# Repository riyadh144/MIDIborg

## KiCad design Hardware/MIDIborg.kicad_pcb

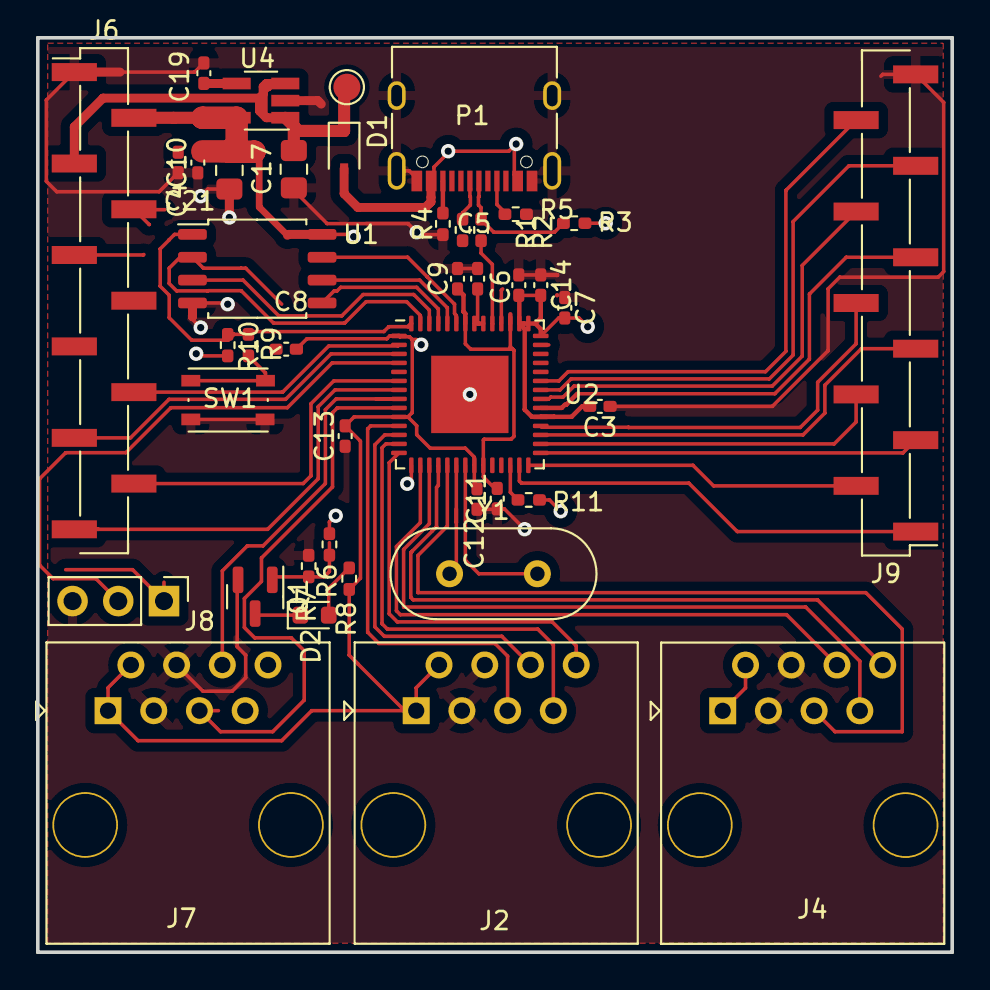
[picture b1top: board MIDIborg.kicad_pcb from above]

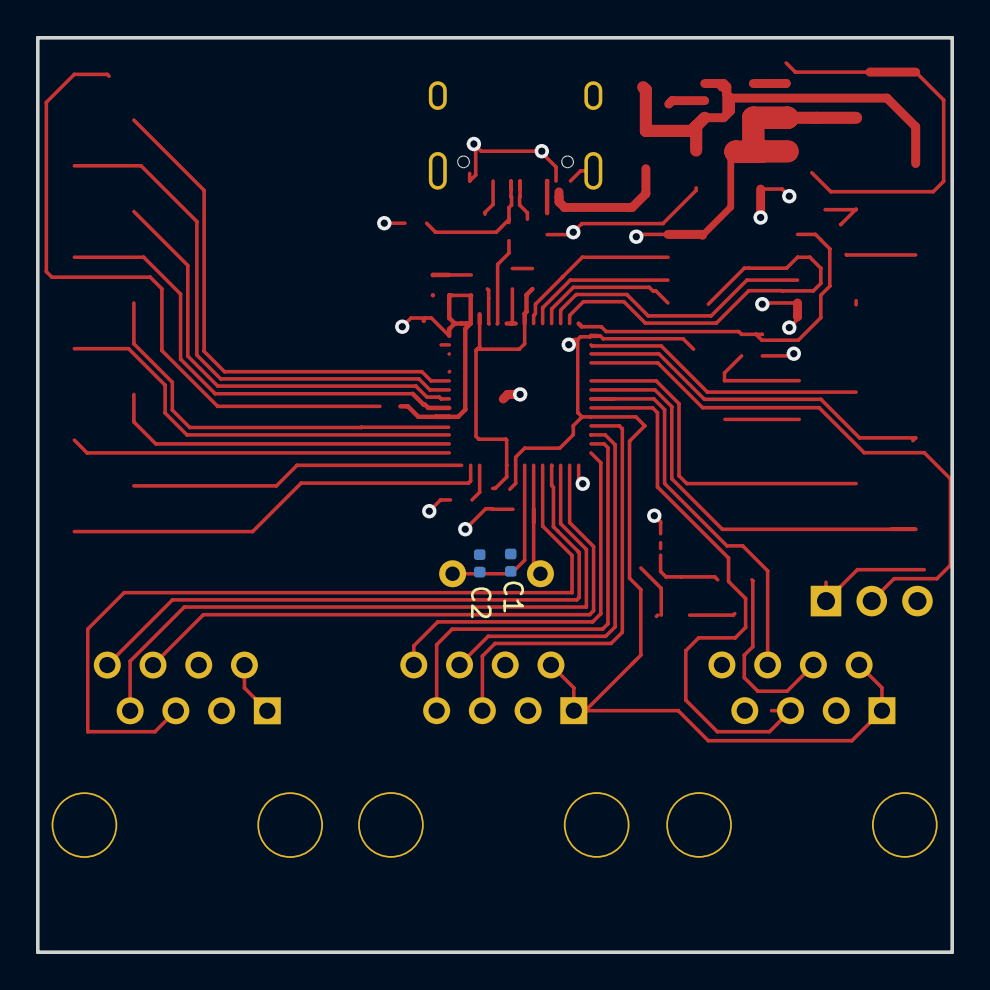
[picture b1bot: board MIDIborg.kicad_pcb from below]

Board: 4 copper layers, 50.8 x 50.8 mm, 44 parts (2 on the bottom side), 52 nets.

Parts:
C1, C2: 18pF; L_0402_1005Metric
C3, C4, C5, C6, C7, C8, C9, C10, C11, C12, C13, C14: .1uF; C_0402_1005Metric_Pad0.74x0.62mm_HandSolder
C17, C21: 1uF; C_0805_2012Metric_Pad1.18x1.45mm_HandSolder
C19: 10nF; C_0402_1005Metric_Pad0.74x0.62mm_HandSolder
D1: 1N5817; D_SOD-323
D2: Red LED; LED_0603_1608Metric
J2, J4, J7: 8P8C; RJ45_OST_PJ012-8P8CX_Vertical
J6, J9: Conn_01x11; PinHeader_1x11_P2.54mm_Vertical_SMD_Pin1Left
J8: Conn_01x03; PinHeader_1x03_P2.54mm_Vertical
P1: USB_C_Plug_USB2.0; USB_C_Receptacle_XKB_U262-16XN-4BVC11
Q1: 2N7002; SOT-23
R1, R2: 27; R_0402_1005Metric_Pad0.72x0.64mm_HandSolder
R3: 1K5; R_0402_1005Metric_Pad0.72x0.64mm_HandSolder
R4, R5: 5k1; R_0402_1005Metric_Pad0.72x0.64mm_HandSolder
R6, R8, R9: 1K; R_0402_1005Metric_Pad0.72x0.64mm_HandSolder
R7: DNP; R_0402_1005Metric_Pad0.72x0.64mm_HandSolder
R10, R11: 10K; R_0402_1005Metric_Pad0.72x0.64mm_HandSolder
SW1: SW_Push; SW_Push_1P1T_NO_Vertical_Wuerth_434133025816
TP2: TestPoint; TestPoint_Pad_D1.5mm
U1: W25Q16JVSSIQ; SOIC-8_5.23x5.23mm_P1.27mm
U2: RP2040; QFN-56-1EP_8x8mm_P0.5mm_EP4.3x4.3mm
U4: BCT2028EUK33; SOT-23-5_HandSoldering
Y1: Crystal; Crystal_HC49-4H_Vertical

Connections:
+3V3: C3.2, C4.2, C5.2, C6.2, C7.2, C8.2, C10.2, C12.2, C13.2, C14.2, C21.2, J2.1, J2.2, J4.1, J4.2, J6.2, J7.1, J7.2, R3.1, R8.1, R10.1, R11.1, U1.8 (VCC), U2.1 (IOVDD), U2.10 (IOVDD), U2.22 (IOVDD), U2.33 (IOVDD), U2.42 (IOVDD), U2.43 (ADC_AVDD), U2.44 (VREG_VIN), U2.48 (USB_VDD), U2.49 (IOVDD), U4.5 (OUT)
+5V: C17.2, D1.1 (K), J6.3, TP2.1, U4.1 (IN), U4.3 (EN)
/1.1V: C9.2, C11.2, U2.23 (DVDD), U2.45 (VREG_VOUT), U2.50 (DVDD)
/GPIO0: J6.8, U2.2 (GPIO0)
/GPIO1: J6.9, U2.3 (GPIO1)
/GPIO4: J6.10, U2.6 (GPIO4)
/GPIO5: J6.11, U2.7 (GPIO5)
/GPIO16: J9.1, U2.27 (GPIO16)
/GPIO17: J9.2, U2.28 (GPIO17)
/GPIO18: J9.3, U2.29 (GPIO18)
/GPIO19: J9.4, U2.30 (GPIO19)
/GPIO20: J9.5, U2.31 (GPIO20)
/GPIO21: J9.6, U2.32 (GPIO21)
/GPIO22: J9.7, U2.34 (GPIO22)
/GPIO23: J9.8, U2.35 (GPIO23)
/GPIO24: J9.9, U2.36 (GPIO24)
/GPIO25: J9.10, U2.37 (GPIO25)
/LED1: R6.2, U2.15 (GPIO12)
/QSPI-CLK: U1.6 (CLK), U2.52 (QSPI_SCLK)
/QSPI-CS: R9.2, R10.2, U1.1 (~CS), U2.56 (QSPI_SS_N)
/QSPI-SD0: U1.5 (DI(IO0)), U2.53 (QSPI_SD0)
/QSPI-SD1: U1.2 (DO(IO1)), U2.55 (QSPI_SD1)
/QSPI-SD2: U1.3 (IO2), U2.54 (QSPI_SD2)
/QSPI-SD3: U1.7 (IO3), U2.51 (QSPI_SD3)
/SCL0: J7.5, U2.9 (GPIO7)
/SDA0: J7.6, U2.8 (GPIO6)
/SPI0_MISO: J4.6, U2.16 (GPIO13)
/SPI0_MOSI: J4.5, U2.19 (TESTEN)
/SPI0_NSS: J4.7, U2.17 (GPIO14)
/SPI0_SCK: J4.8, U2.18 (GPIO15)
/SPI1_MISO: J2.6, U2.12 (GPIO9)
/SPI1_MOSI: J2.5, U2.11 (GPIO8)
/SPI1_NSS: J2.7, U2.13 (GPIO10)
/SPI1_SCK: J2.8, U2.14 (GPIO11)
/UART1_RX: J8.1, U2.5 (GPIO3)
/UART1_TX: J8.2, U2.4 (GPIO2)
/USB_BOOT: R9.1, SW1.1
/d+: R2.1, U2.47 (USB_DP)
/d-: R1.2, U2.46 (USB_DM)
/dd+: P1.A6 (D+), R2.2, R3.2
/dd-: P1.A7 (D-), R1.1
GND: C1.2, C2.2, C3.1, C4.1, C5.1, C6.1, C7.1, C8.1, C9.1, C10.1, C11.1, C12.1, C13.1, C14.1, C17.1, C19.1, C21.1, J2.3, J2.4, J4.3, J4.4, J6.1, J7.3, J7.4, J8.3, J9.11, P1.A1 (GND), P1.A12 (GND), P1.B1 (GND), P1.B12 (GND), P1.S1 (SHIELD), Q1.2 (S), R4.2, R5.2, R7.2, SW1.2, U1.4 (GND), U2.57 (GND), U4.2 (GND)
unnamed: C1.1, U2.20 (XIN), Y1.1
unnamed: C2.1, U2.21 (XOUT), Y1.2
unnamed: C19.2, U4.4 (BP)
unnamed: D1.2 (A), P1.A4 (VBUS), P1.A9 (VBUS), P1.B4 (VBUS), P1.B9 (VBUS)
unnamed: D2.1 (K), Q1.3 (D)
unnamed: D2.2 (A), R8.2
unnamed: P1.A5 (CC), R5.1
unnamed: P1.B5 (VCONN), R4.1
unnamed: Q1.1 (G), R6.1, R7.1
unnamed: R11.2, U2.26 (RUN)

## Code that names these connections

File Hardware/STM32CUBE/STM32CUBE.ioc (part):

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Mcu.Name=STM32F411V(C-E)Tx
Mcu.Package=LQFP100
Mcu.UserName=STM32F411VETx
PA0-WKUP.Signal=ADCx_IN0
PA1.Signal=ADCx_IN1
PA10.Mode=Asynchronous
PA10.Signal=USART1_RX
PA11.Mode=Device_Only
PA11.Signal=USB_OTG_FS_DM
PA12.Mode=Device_Only
PA12.Signal=USB_OTG_FS_DP
PA15.Mode=NSS_Signal_Hard_Output
PA15.Signal=SPI1_NSS
PA2.Signal=ADCx_IN2
PA3.Signal=ADCx_IN3
PA4.Signal=ADCx_IN4
PA5.Signal=ADCx_IN5
PA6.Signal=ADCx_IN6
PA7.Signal=ADCx_IN7
PA9.Mode=Asynchronous
PA9.Signal=USART1_TX
PB0.Signal=ADCx_IN8
PB1.Signal=ADCx_IN9
PB3.Mode=Full_Duplex_Master
PB3.Signal=SPI1_SCK
PB4.Mode=Full_Duplex_Master
PB4.Signal=SPI1_MISO
PB5.Mode=Full_Duplex_Master
PB5.Signal=SPI1_MOSI
PC0.Signal=ADCx_IN10
PC1.Signal=ADCx_IN11
PC10.Mode=SD_4_bits_Wide_bus
PC10.Signal=SDIO_D2
PC11.Mode=SD_4_bits_Wide_bus
PC11.Signal=SDIO_D3
PC12.Mode=SD_4_bits_Wide_bus
PC12.Signal=SDIO_CK
PC2.Signal=ADCx_IN12
PC3.Signal=ADCx_IN13
PC4.Signal=ADCx_IN14
PC5.Signal=ADCx_IN15
PC8.Mode=SD_4_bits_Wide_bus
PC8.Signal=SDIO_D0
PC9.Mode=SD_4_bits_Wide_bus
PC9.Signal=SDIO_D1
PD2.Mode=SD_4_bits_Wide_bus
PD2.Signal=SDIO_CMD
PH0\ -\ OSC_IN.Mode=HSE-External-Oscillator
PH0\ -\ OSC_IN.Signal=RCC_OSC_IN
PH1\ -\ OSC_OUT.Mode=HSE-External-Oscillator
PH1\ -\ OSC_OUT.Signal=RCC_OSC_OUT
RCC.HSE_VALUE=8000000
RCC.SYSCLKFreq_VALUE=16000000
board=custom

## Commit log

2022-01-15 Initial copy of library
2022-01-15 I'll try the whole repo
2022-01-15 Initial commit of Majenko library
2022-01-15 Adding other stuff
2022-01-15 Structuring program
2022-01-15 Switching to a different MCP23 library
    Initial
2022-01-15 Schematics
2022-01-16 This is a mess. Changing uCs
2022-01-16 Transition to RP2040
2022-01-16 Finished Schematics and placed most components
2022-01-16 Finished layout
2022-01-16 creating project
2022-01-16 Adding build folder
2022-02-05 One layer Midiborg
